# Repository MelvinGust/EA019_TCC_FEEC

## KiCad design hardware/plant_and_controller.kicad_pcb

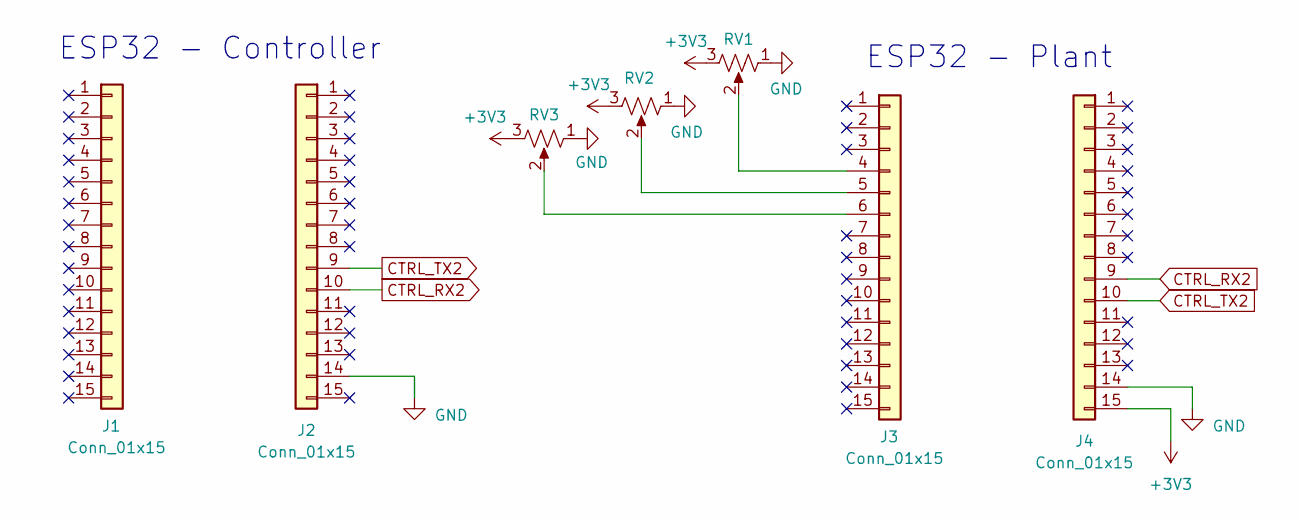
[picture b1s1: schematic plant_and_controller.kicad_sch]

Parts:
J1, J2, J3, J4: Conn_01x15; PinHeader_1x15_P2.54mm_Vertical
RV1, RV2, RV3: R_Potentiometer_US; Potentiometer_Alps_RK163_Single_Horizontal

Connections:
+3V3: J4.15, RV1.3, RV2.3, RV3.3
CTRL_RX2: J2.10, J4.9
CTRL_TX2: J2.9, J4.10
GND: J2.14, J4.14, RV1.1, RV2.1, RV3.1
unnamed: J3.4, RV1.2
unnamed: J3.5, RV2.2
unnamed: J3.6, RV3.2

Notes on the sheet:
ESP32 - Plant
ESP32 - Controller

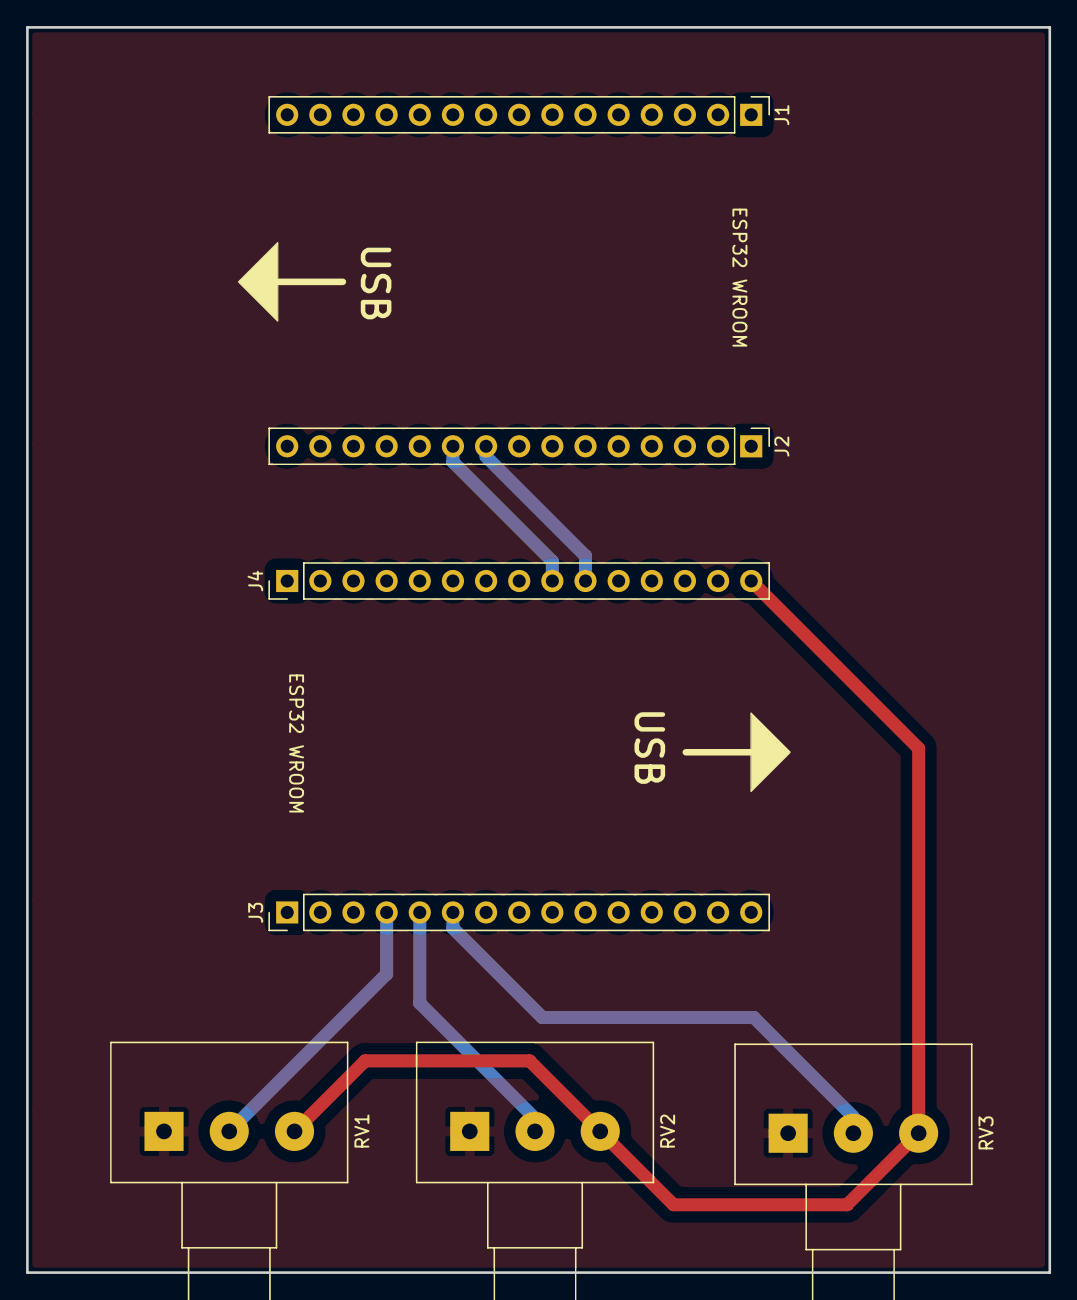
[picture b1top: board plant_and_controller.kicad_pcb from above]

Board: 2 copper layers, 78.3 x 95.4 mm, 7 parts (0 on the bottom side), 7 nets.
